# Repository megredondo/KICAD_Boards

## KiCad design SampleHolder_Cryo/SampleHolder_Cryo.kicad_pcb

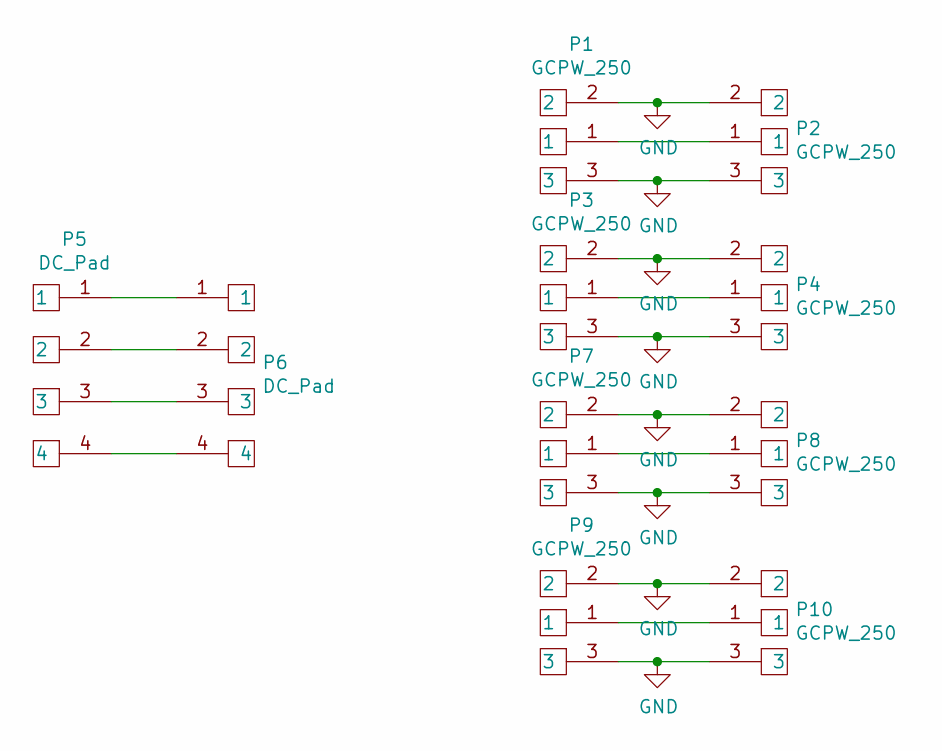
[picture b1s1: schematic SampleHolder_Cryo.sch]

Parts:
P1, P2, P3, P4, P7, P8, P9, P10: GCPW_250; GCPW_0.254_SH
P5: DC_Pad; Pin_Strip
P6: DC_Pad; DC_Lines_SH

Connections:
GND: P1.2, P1.3, P2.2, P2.3, P3.2, P3.3, P4.2, P4.3, P7.2, P7.3, P8.2, P8.3, P9.2, P9.3, P10.2, P10.3
unnamed: P1.1, P2.1
unnamed: P3.1, P4.1
unnamed: P5.1, P6.1
unnamed: P5.2, P6.2
unnamed: P5.3, P6.3
unnamed: P5.4, P6.4
unnamed: P7.1, P8.1
unnamed: P9.1, P10.1

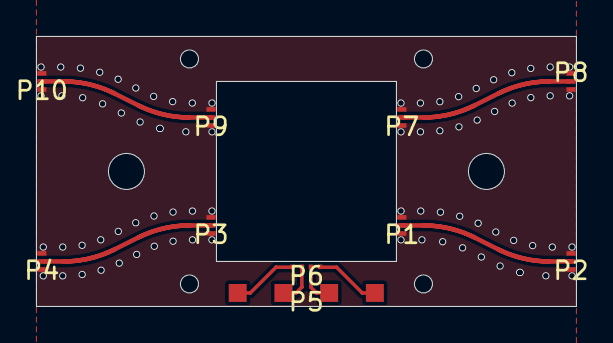
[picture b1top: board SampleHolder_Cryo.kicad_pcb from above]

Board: 2 copper layers, 30.0 x 15.0 mm, 10 parts (0 on the bottom side), 9 nets.

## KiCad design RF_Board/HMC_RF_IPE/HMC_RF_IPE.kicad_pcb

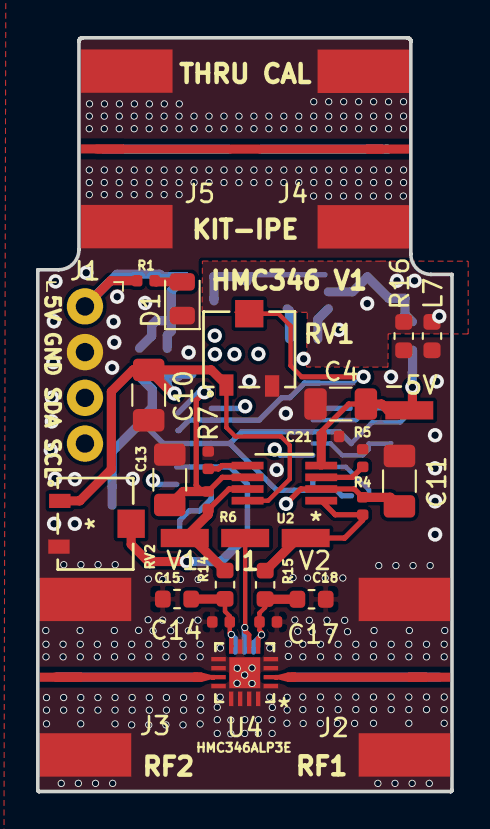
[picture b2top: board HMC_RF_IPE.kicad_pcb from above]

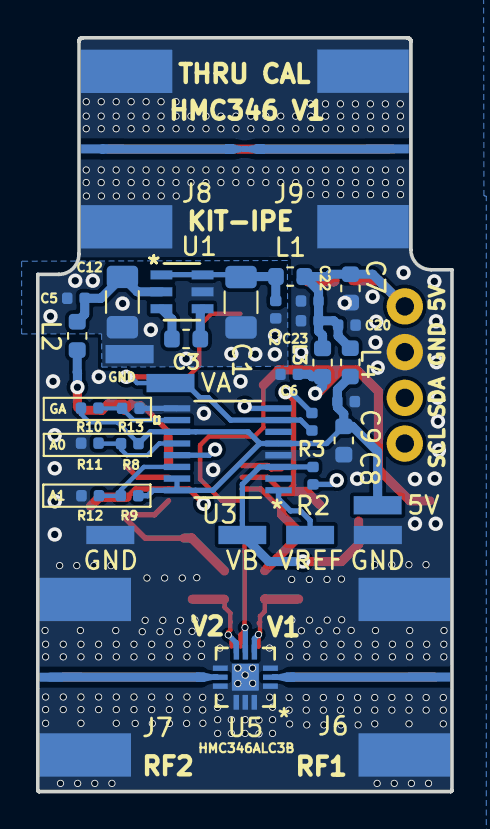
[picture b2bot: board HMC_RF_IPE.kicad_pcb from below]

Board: 4 copper layers, 23.0 x 41.9 mm, 75 parts (41 on the bottom side), 35 nets.

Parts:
5V: 5V; Test_Point_2.67x1.02mm
-5V: -5V; Test_Point_2.67x1.02mm
C1, C4, C10, C12: 10u; C_1206_3216Metric
C2, C5, C6, C9, C20, C21, C22, C23: 100n; C_0402_1005Metric
C3, C7, C8: 1u; C_0603_1608Metric
C11, C13: 22u; C_1206_3216Metric
C14, C17: 10n; C_0402_1005Metric
C15, C18: 100n; C_0603_1608Metric
D1: LED; LED_0805_2012Metric
GND: GND; Test_Point_2.67x1.02mm
GND#2, GND#3: GND; Test_Point_2.67x1.02mm
I1: I; Test_Point_2.67x1.02mm
J1: Data; PinHeader_1x4_P2.54mm_Drill1.02mm
J2, J3, J4, J5, J6, J7, J8, J9: Conn_Coaxial; SMA_142_0701_851
L1, L2, L3, L4, L7: L; L_0603_1608Metric
R1: 5K 1%; R_0402_1005Metric
R2, R3, R4, R6: 10K 1%; R_0402_1005Metric
R5, R7: 4.99K 1%; R_0402_1005Metric
R8, R9, R10, R11, R12, R13: DNP; R_0402_1005Metric
R14, R15: 0; R_0603_1608Metric
R16: 10; R_0603_1608Metric
RV1, RV2: R_POT_TRIM; 3214W-1-103E
U1: LTC1983ES6-5-TRMPBF
U2: ADA4896-2ARMZ
U3: AD5697RBCPZ-RL7; AD5697RBRUZ
U4: HMC346ALP3E
U5: HMC346ALC3B
U6: Tap_Cout; uwT0.50_0.51_0.30_0.30_0.6_double
V1: V1; Test_Point_2.67x1.02mm
V2: V2; Test_Point_2.67x1.02mm
VA: VB; Test_Point_2.67x1.02mm
VB: VA; Test_Point_2.67x1.02mm
VREF: VREF; Test_Point_2.67x1.02mm
uT1, uT2: Taper; uwT0.50_0.51_0.30_0.30_0.60
uT3, uT4: Taper; uwT0.50_0.51_0.20_0.25_0.60

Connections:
+5V: C7.2, C20.1, C22.1, C23.1, J1.1, L1.1, L3.1, L4.1, R1.1
/Control/I: I1.1, U4.6, U5.5
/Control/V1: R6.1, R14.1, U2.7, V1.1
/Control/V2: R4.1, R15.1, U2.1, V2.1
GND: C4.2, C6.2, C7.1, C8.2, C9.2, C10.2, C11.2, C13.2, C14.2, C15.2, C17.2, C18.2, C20.2, C21.2, C22.2, C23.2, D1.1, GND#2.1, GND#3.1, J1.2, J2.2, J3.2, J4.2, J5.2, L7.2, R5.2, R7.2, R11.1, R12.1, R13.1, R16.1, RV1.3, RV2.3, U3.4, U3.9, U4.1, U4.3, U4.4, U4.7, U4.9, U4.10, U4.12, U4.13, U4.14, U4.15, U4.16, U4.17, U5.1, U5.3, U5.7, U5.9, U5.10, U5.11, U5.12, U5.13
GNDS: C1.2, C2.2, C5.2, C12.2, GND.1, L7.1, R16.2, U1.5
unnamed: 5V.1, C8.1, C9.1, L4.2, R8.2, R9.2, R10.2, U3.5, U3.11, U3.15, U3.16
unnamed: C1.1, C2.1, L1.2, U1.1, U1.6
unnamed: C3.1, U1.3
unnamed: C3.2, U1.4
unnamed: C6.1, C10.1, L3.2, RV1.1, RV2.1, U2.8
unnamed: C11.1, R2.1, R4.2, U2.2
unnamed: C5.1, C12.1, L2.2, U1.2
unnamed: C13.1, R3.1, R6.2, U2.6
unnamed: C14.1, C15.1, R14.2, U4.8, U5.4
unnamed: C17.1, C18.1, R15.2, U4.5, U5.6
unnamed: D1.2, R1.2
unnamed: J1.3, U3.8
unnamed: J1.4, U3.13
unnamed: J2.1, U4.2, uT3.1
unnamed: J3.1, U4.11, uT4.1
unnamed: J4.1, J5.1
unnamed: J6.1, U5.2, uT1.1
unnamed: J7.1, U5.8, uT2.1
unnamed: J8.1, U6.1
unnamed: J9.1, U6.2
unnamed: R2.2, RV2.2, U3.3, VB.1
unnamed: R3.2, RV1.2, U3.7, VA.1
unnamed: R5.1, U2.3
unnamed: R7.1, U2.5
unnamed: R10.1, R13.2, U3.10
unnamed: R8.1, R11.2, U3.12
unnamed: R9.1, R12.2, U3.14
unnamed: U3.1, VREF.1
VSS: -5V.1, C4.1, C21.1, L2.1, U2.4

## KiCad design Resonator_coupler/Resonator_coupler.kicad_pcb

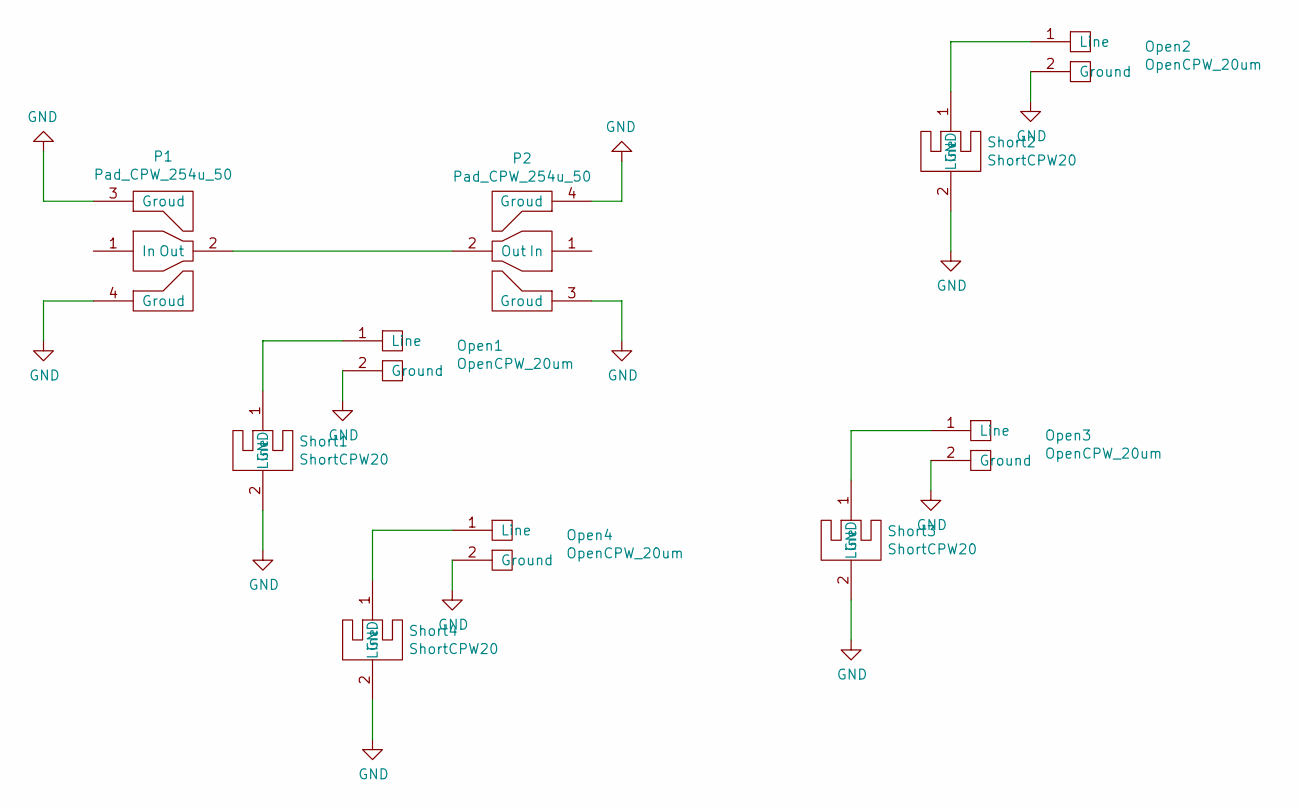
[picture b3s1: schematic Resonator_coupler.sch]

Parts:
Open1, Open2, Open3, Open4: OpenCPW_20um; Open_CPW_20um
P1, P2: Pad_CPW_254u_50; Pad_100um_Pitch_Silicon_50
Short1, Short2, Short3, Short4: ShortCPW20; Short_CPW_20um

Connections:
GND: Open1.2 (Ground), Open2.2 (Ground), Open3.2 (Ground), Open4.2 (Ground), P1.3 (Groud), P1.4 (Groud), P2.3 (Groud), P2.4 (Groud), Short1.2 (GND), Short2.2 (GND), Short3.2 (GND), Short4.2 (GND)
unnamed: Open1.1 (Line), Short1.1 (Line)
unnamed: Open2.1 (Line), Short2.1 (Line)
unnamed: Open3.1 (Line), Short3.1 (Line)
unnamed: Open4.1 (Line), Short4.1 (Line)
unnamed: P1.2 (Out), P2.2 (Out)

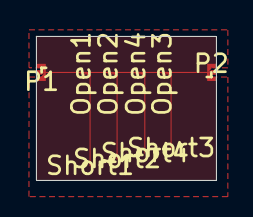
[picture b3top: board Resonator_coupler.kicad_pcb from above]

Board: 2 copper layers, 10.0 x 8.0 mm, 10 parts (0 on the bottom side), 6 nets.

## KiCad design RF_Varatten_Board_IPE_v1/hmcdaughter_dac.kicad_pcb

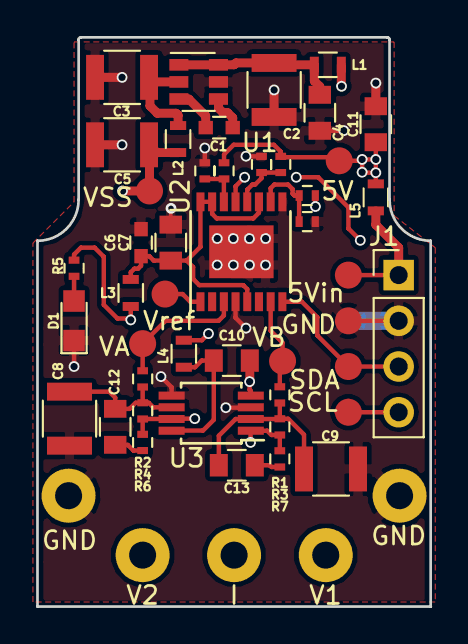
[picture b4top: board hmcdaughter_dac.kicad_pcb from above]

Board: 4 copper layers, 21.9 x 31.6 mm, 50 parts (0 on the bottom side), 25 nets.

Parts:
C1, C6: 1uF; C_0603
C2, C3, C5: 10uF; C_1210
C4, C7, C10, C11: 100nF; C_0805
C8, C9: 22uF; C_1210
C12, C13: 10nF; C_0805
D1: LED; LED_0805
J1: CONN_01X04_MALE; Pin_Header_Straight_1x04_Pitch2.54mm
L1, L2, L3, L4, L5: ?nH; L_0603
R1, R2: 10k; R_0402
R3, R4: 20k; R_0402
R5: 5k; R_0402
R6, R7: 100; R_0402
R8, R9, R10, R11, R12, R13: 0; R_0402
TP1: 5Vin; Measurement_Point_Round-SMD-Pad_Small
TP2, TP3: GND; Measurement_Point_Round-TH_Big
TP4: GND; Measurement_Point_Round-SMD-Pad_Small
TP5: SCL; Measurement_Point_Round-SMD-Pad_Small
TP6: SDA; Measurement_Point_Round-SMD-Pad_Small
TP7: VSS; Measurement_Point_Round-SMD-Pad_Small
TP8: Vref; Measurement_Point_Round-SMD-Pad_Small
TP9: VA; Measurement_Point_Round-SMD-Pad_Small
TP10: VB; Measurement_Point_Round-SMD-Pad_Small
TP11: V1; Measurement_Point_Round-TH_Big
TP12: V2; Measurement_Point_Round-TH_Big
TP13: I; Measurement_Point_Round-TH_Big
TP14: 5V; Measurement_Point_Round-SMD-Pad_Small
U1: LTC1983; SOT-23-6
U2: AD5697R_TSSOP; TSSOP-16-1EP_4.4x5mm_Pitch0.65mm
U3: ADA4896; MSOP-8_3x3mm_Pitch0.65mm

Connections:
+5V: C11.1, L1.2, L3.1, L4.1, L5.1, R5.2, R8.1, R10.1, R12.2, TP14.1
/SCL: J1.4, TP5.1, U2.13
/SDA: J1.3, TP6.1, U2.8
/VA: R2.2, TP9.1, U2.3
/VB: R1.2, TP10.1, U2.7
GND: C2.2, C3.2, C4.2, C5.2, C6.2, C7.2, C8.2, C9.2, C11.2, D1.1, J1.2, R9.2, R11.2, R13.2, TP2.1, TP3.1, TP4.1, U1.5, U2.4, U2.9, U2.17, U3.3, U3.5
unnamed: C1.1, U1.3
unnamed: C1.2, U1.4
unnamed: C2.1, C4.1, L1.1, U1.1, U1.6
unnamed: C3.1, L2.2, U1.2
unnamed: C6.1, C7.1, L3.2, U2.5, U2.11, U2.15, U2.16
unnamed: C10.2, L4.2, U3.8
unnamed: C12.1, R6.2
unnamed: C8.1, C12.2, R2.1, R4.2, U3.6
unnamed: C13.1, R7.2
unnamed: C9.1, C13.2, R1.1, R3.2, U3.2
unnamed: D1.2, R5.1
unnamed: J1.1, L5.2, TP1.1
unnamed: R3.1, R7.1, TP11.1, U3.1
unnamed: R4.1, R6.1, TP12.1, U3.7
unnamed: R8.2, R9.1, U2.14
unnamed: R10.2, R11.1, U2.12
unnamed: R12.1, R13.1, U2.10
unnamed: TP8.1, U2.1
VSS: C5.1, C10.1, L2.1, TP7.1, U3.4

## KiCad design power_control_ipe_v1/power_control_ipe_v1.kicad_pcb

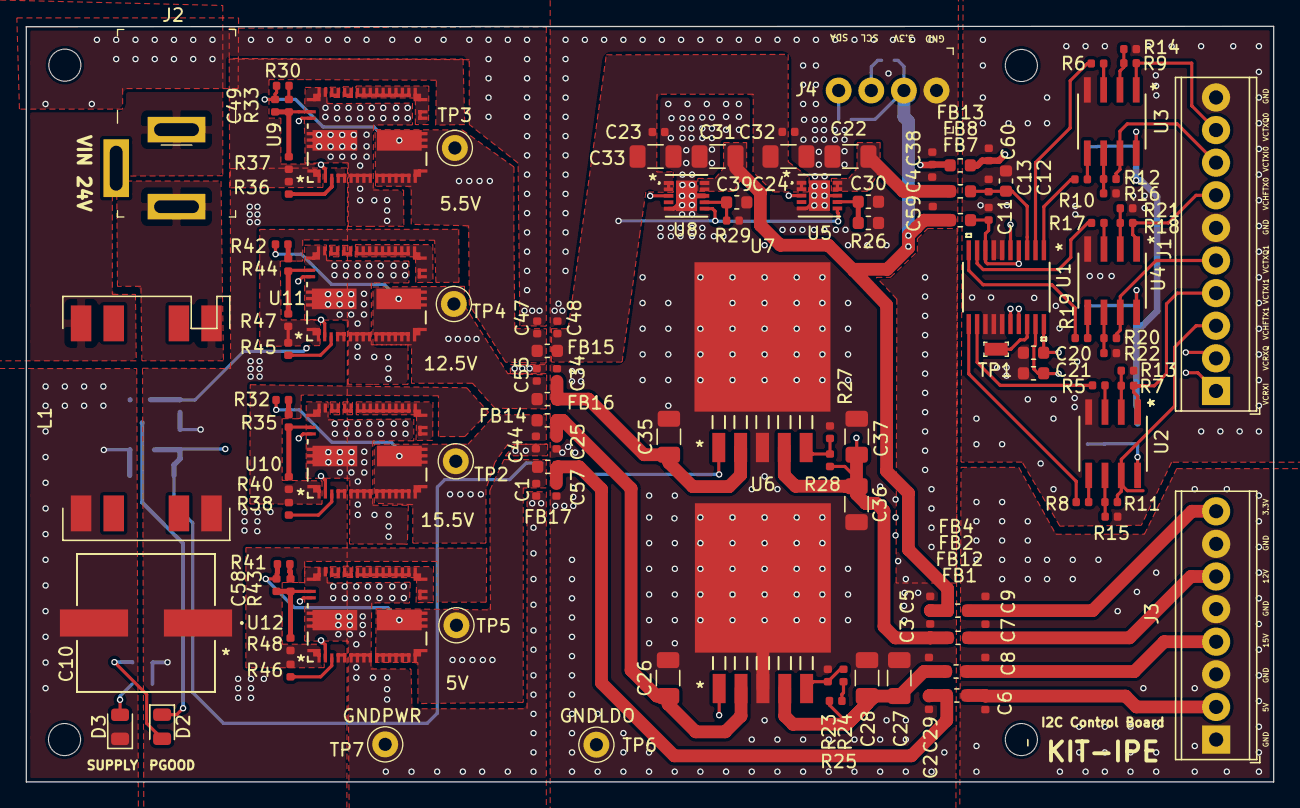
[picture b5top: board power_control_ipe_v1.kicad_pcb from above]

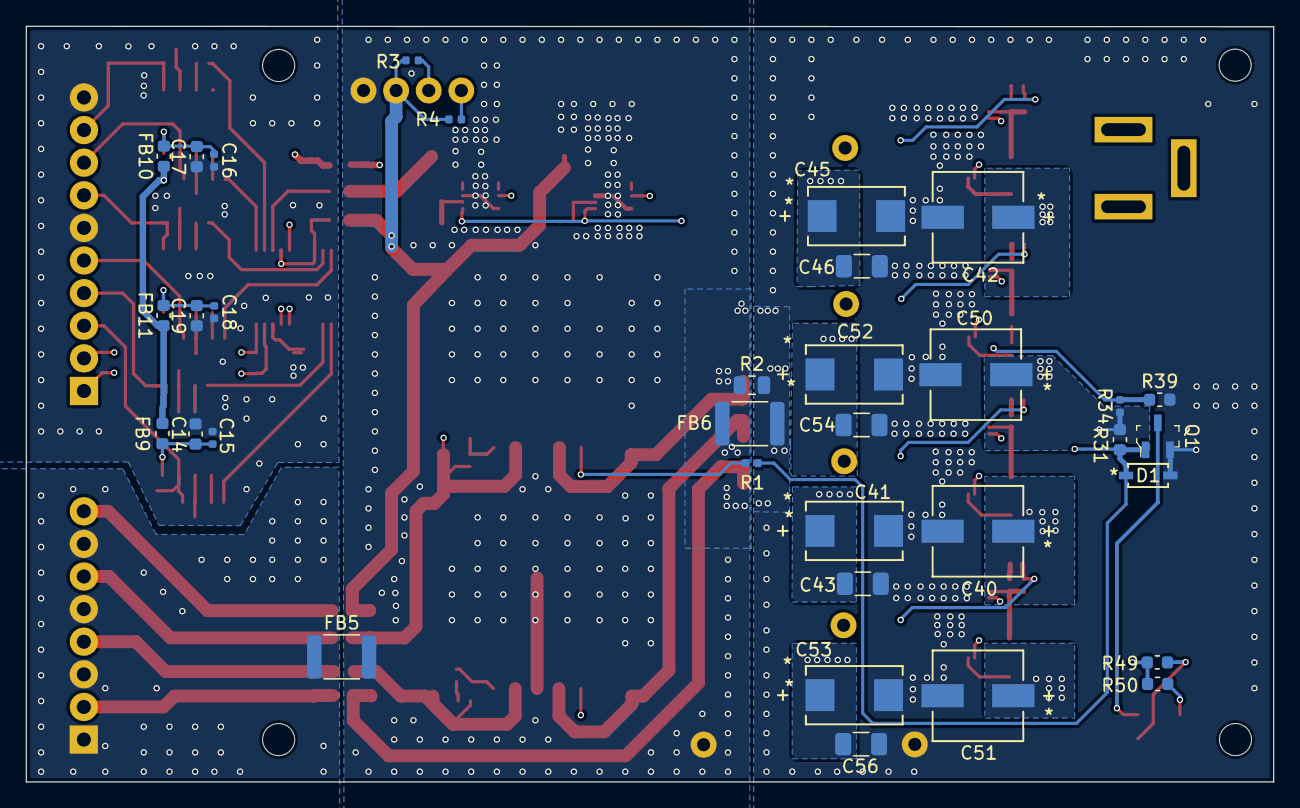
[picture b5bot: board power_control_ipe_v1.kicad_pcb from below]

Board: 4 copper layers, 97.2 x 58.9 mm, 158 parts (34 on the bottom side), 88 nets.

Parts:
C1, C2, C3, C4, C5, C6, C7, C8, C9, C11, C13, C14, C16, C18, C23, C25, C29, C32, C34, C38, C44, C47, C48, C55, C57, C59, C60: 100n 25V; C_0402_1005Metric
C10: EEEFP1V331AP
C12: 10u 16V; C_0603_1608Metric
C15, C17, C19, C20, C21: 1u 16V; C_0603_1608Metric
C22, C24, C27, C28, C31, C33, C36, C37, C43, C54, C56: 22u 25V; C_1206_3216Metric
C26, C35: 10u 25V; C_1206_3216Metric
C30, C39: 470n 16V; C_0603_1608Metric
C40, C42, C50, C51: UCD1H470MCL1GS
C41, C45, C52, C53: TCSCS1D470KDAR; T495D476K020ASE175
C46: 47u 25V; C_1206_3216Metric
C49, C58: 82p 25V; C_0402_1005Metric
D1: DDZ9681-7
D2, D3: LED; LED_0805_2012Metric
FB1, FB2, FB4, FB7, FB8, FB9, FB10, FB11, FB12, FB13, FB14, FB15, FB16, FB17: Ferrite_Bead 2A; L_0603_1608Metric
FB5, FB6: Ferrite_Bead 3A; L_1812_4532Metric
H1, H2, H3, H4: MountingHole; MountingHole_2.5mm
J1: Screw_Terminal_01x10; TerminalBlock_Phoenix_MPT-0,5-10-2.54_1x10_P2.54mm_Horizont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
J2: Jack-DC; Barrel_Jack_5.5mmODx2.1mmID_PJ-202A
J3: Screw_Terminal_01x08; TerminalBlock_Phoenix_MPT-0,5-8-2.54_1x08_P2.54mm_Horizontal
J4: 0022232041; PinHeader_1x4_P2.54mm_Drill1.02mm
L1: WE-UCF_2TURNS_744290321
Q1: BSS138; SOT-23-3
R1, R33: 2K 1%; R_0402_1005Metric
R2: 100; R_0805_2012Metric
R3, R4: DNP; C_0402_1005Metric
R5, R6, R8, R10, R17, R19: 1K 0.1%; R_0402_1005Metric
R7, R9, R11, R12, R13, R14, R15, R16, R18, R20, R21, R22: 2K 0.1%; R_0402_1005Metric
R23: 3.9K 5%; R_0402_1005Metric
R24, R30: 43K 1%; R_0402_1005Metric
R25: 1.2K 1%; R_0402_1005Metric
R26: 51K 0.1%; R_0603_1608Metric
R27: 4.12K 0.1%; R_0402_1005Metric
R28: 36.5K 0.1%; R_0402_1005Metric
R29: 33K 1%; R_0402_1005Metric
R31: 100K 1%; R_0603_1608Metric
R32: 130K 1%; R_0402_1005Metric
R34: 100K 1%; R_0402_1005Metric
R35: 15K 1%; R_0402_1005Metric
R36, R46: 82K 1%; R_0402_1005Metric
R37, R40, R47, R48: 10K 1%; R_0402_1005Metric
R38, R45: 39K 1%; R_0402_1005Metric
R39: 7.5K 1%; R_0603_1608Metric
R41, R43: 20K 1%; R_0402_1005Metric
R42: 110K 1%; R_0402_1005Metric
R44: 5.1K 1%; R_0402_1005Metric
R49, R50: 3.3K 1%; R_0603_1608Metric
TP1: TestPoint; PROBE_PAD_0603
TP2, TP3, TP4, TP5, TP6, TP7: TestPoint; Test_Point_D1.02mm
U1: AD5675RBRUZ; AD5675ARUZ
U2, U3, U4: LT6201-EDIT; LT6201IS8-TRPBF
U5, U8: LT3045EDD-TRPBF
U6, U7: LT1963EQ-PBF
U9, U10, U11, U12: LMZM33602RLRR

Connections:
3.3V: C9.2, FB4.2, J3.8
3.3V_LDO: C5.2, C31.1, C59.2, FB4.1, FB7.1, J4.2, R3.2, R4.1, U8.9, U8.10
5V_UN: C6.2, FB1.2, J3.2
12V: C7.2, FB2.2, J3.6
15V: C8.2, FB12.1, J3.4
24V: C10.1, C40.1, C42.1, C50.1, C51.1, L1.10, R31.1, R34.1, R49.1, R50.1, U9.4, U10.4, U11.4, U12.4
/DAC/VD5V: C4.2, C22.1, FB8.2, U5.9, U5.10
/DC-DC Converters/PGOOD: D1.1, Q1.1, R1.2, R31.2, U9.17, U10.17, U11.17, U12.17
/DC-DC Converters/VOUT_5V: C1.2, C2.2, FB1.1, FB17.1
/LDO Regulators/LDO_EN: R1.1, U5.3, U6.1, U7.1, U8.3
/LDO Regulators/VIN_5.5V: C23.1, C24.1, C32.1, C33.1, C48.2, FB15.1, U5.1, U5.2, U5.6, U8.1, U8.2, U8.6
/LDO Regulators/VIN_12.5V: C34.1, C35.1, FB16.2, U7.2
/LDO Regulators/VIN_15.5V: C25.1, C26.1, FB14.1, U6.2
/LDO Regulators/VOUT_12V: C3.2, C36.1, C37.1, C38.1, FB2.1, FB13.2, R28.1, U7.4
/OP Amps/VIN1: R6.2, U1.2
/OP Amps/VIN2: R10.1, U1.1
/OP Amps/VIN5: R8.1, U1.11
/OP Amps/VIN6: R5.2, U1.12
/OP Amps/VIN7: R19.1, U1.10
/OP Amps/VIN8: R17.2, U1.9
/OP Amps/VIN_12V: C60.1, FB9.1, FB10.1, FB11.1, FB13.1
EN: R34.2, R39.1, U9.2, U10.2, U11.2, U12.2
Earth: J2.2, L1.5
GND: C1.1, C2.1, C3.1, C4.1, C5.1, C11.2, C12.2, C13.2, C14.2, C15.1, C16.2, C17.1, C18.2, C19.1, C20.2, C21.2, C22.2, C23.2, C24.2, C25.2, C26.2, C27.2, C28.2, C29.2, C30.2, C31.2, C32.2, C33.2, C34.2, C35.2, C36.2, C37.2, C38.2, C39.2, C48.1, C59.1, C60.2, FB5.2, FB6.1, J1.6, J1.10, J4.1, R2.1, R13.2, R14.2, R15.2, R16.2, R21.2, R22.2, R23.2, R26.1, R27.2, R29.1, TP6.1, U1.6, U1.7, U1.13, U1.14, U1.15, U2.4, U3.4, U4.4, U5.5, U5.8, U5.11, U6.3, U6.6, U7.3, U7.6, U8.5, U8.8, U8.11
GNDPWR: C10.2, C40.2, C41.2, C42.2, C43.2, C44.2, C45.2, C46.2, C47.2, C50.2, C51.2, C52.2, C53.2, C54.2, C55.2, C56.2, C57.2, D1.2, D3.1, FB6.2, L1.6, Q1.2, R2.2, R39.2, TP7.1, U9.5, U9.14, U9.15, U9.18, U10.5, U10.14, U10.15, U10.18, U11.5, U11.14, U11.15, U11.18, U12.5, U12.14, U12.15, U12.18
GNDREF: C6.1, C7.1, C8.1, C9.1, FB5.1, J3.1, J3.3, J3.5, J3.7
unnamed: C11.1, FB7.2, U1.4, U1.8, U1.17
unnamed: C12.1, C13.1, FB8.1, U1.3
unnamed: C14.1, C15.2, FB9.2, U2.8
unnamed: C16.1, C17.2, FB10.2, U3.8
unnamed: C18.1, C19.2, FB11.2, U4.8
unnamed: C27.1, C28.1, C29.1, FB12.2, R25.1, U6.4
unnamed: C30.1, R26.2, U5.7
unnamed: C39.1, R29.2, U8.7
unnamed: C41.1, C43.1, C44.1, FB14.2, R32.1, TP2.1, U10.6, U10.7, U10.8
unnamed: C45.1, C46.1, C47.1, C49.1, FB15.2, R30.1, TP3.1, U9.6, U9.7, U9.8
unnamed: C49.2, R33.2, R37.1, U9.16
unnamed: C52.1, C54.1, C55.1, FB16.1, R42.1, TP4.1, U11.6, U11.7, U11.8
unnamed: C53.1, C56.1, C57.1, C58.1, FB17.2, R41.1, TP5.1, U12.6, U12.7, U12.8
unnamed: C58.2, R43.2, R48.1, U12.16
unnamed: D2.1, Q1.3
unnamed: D2.2, R49.2
unnamed: D3.2, R50.2
unnamed: J2.1, L1.1
unnamed: R5.1, U2.3
unnamed: R6.1, U3.3
unnamed: R8.2, U2.5
unnamed: R10.2, U3.5
unnamed: R11.1, R15.1, U2.6
unnamed: R12.1, R16.1, U3.6
unnamed: R7.1, R13.1, U2.2
unnamed: R9.1, R14.1, U3.2
unnamed: R17.1, U4.3
unnamed: R18.1, R21.1, U4.2
unnamed: R19.2, U4.5
unnamed: R20.1, R22.1, U4.6
unnamed: R23.1, R24.2, U6.5
unnamed: R24.1, R25.2
unnamed: R27.1, R28.2, U7.5
unnamed: R30.2, R33.1
unnamed: R32.2, R35.2
unnamed: R35.1, R40.1, U10.16
unnamed: R36.1, U9.3
unnamed: R36.2, R37.2, U9.1
unnamed: R38.1, U10.3
unnamed: R38.2, R40.2, U10.1
unnamed: R41.2, R43.1
unnamed: R42.2, R44.1
unnamed: R44.2, R47.1, U11.16
unnamed: R45.1, U11.3
unnamed: R45.2, R47.2, U11.1
unnamed: R46.1, U12.3
unnamed: R46.2, R48.2, U12.1
unnamed: U9.9, U9.10, U9.11
unnamed: U10.9, U10.10, U10.11
unnamed: U11.9, U11.10, U11.11
unnamed: U12.9, U12.10, U12.11
SCL: J4.3, R3.1, U1.5
SDA: J4.4, R4.2, U1.16
VCHFTX0: J1.7, R18.2, U4.1
VCHFTX1: J1.3, R11.2, U2.7
VCRXI: C21.1, J1.1, U1.19
VCRXQ: C20.1, J1.2, U1.20
VCTXI0: J1.8, R12.2, U3.7
VCTXI1: J1.4, R7.2, U2.1
VCTXQ0: J1.9, R9.2, U3.1
VCTXQ1: J1.5, R20.2, U4.7
VREF: TP1.1, U1.18

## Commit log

2020-06-18 Boards v1.0
2020-07-23 hola
2020-07-26 new boards
2020-10-06 Sample holder

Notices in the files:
parts and their libraries:
Copyright 2016 Accelerated Designs. All rights reserved.
